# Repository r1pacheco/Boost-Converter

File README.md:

# Boost-Converter

<h3>This board was designed specifically for the R3 rover and has major restraints that were followed: </h3>

* Maximum dimensions of 42mm x 48mm x 23mm to remain inside the restrictions of the PDB (Power Distribution Board)
* Header space is required so parts do not overlap or bump edges as it is a tight fit within the chasis and the Molex connectors 
* Needs to handle a minimum of 5 amps and increase voltage from 15 to 24 volts minimum (my actual design uses a 5KΩ potentiometer to vary the desired voltage at the output, to make it more flexible for future use if needed)

|Top Side|Bottom Side|
|---|---|
|||  

*Click the above photos for a larger view*

<h3>Details and considerations made to improve the boards design and functionality:</h3>

* Thick traces or polygons are used to handle large current as well as act as heat displacers 
* Room for large external heat sinks was needed to help cool down the MOSFET and large diode on the board since they handle the bulk of the current
* Vias were also used to help give direct air flow to the main IC and fuse holder 
* a physical cutout (notch) was placed in the PCB beside the horizontal fuse holder, making it easier to set/remove the fuses (they can be tight sometimes)
* Large polygons were used where the most current would travel to make sure traces did not burn up and can disipate as much heat as possible
* all large capacitors/inductors were kept to one side of the board so they would not interfere with external Molex connectors on the PDB board. This is needed since the right side of the board will be overlapping pre-existing components and we needed the compensated space
* LED indication tells the user if the board is being used and is working properly
* overall board size was given tolerances of 1mm x 1mm x 1mm so they did not interfere with other external boards. Chamfers were also added for the same reason

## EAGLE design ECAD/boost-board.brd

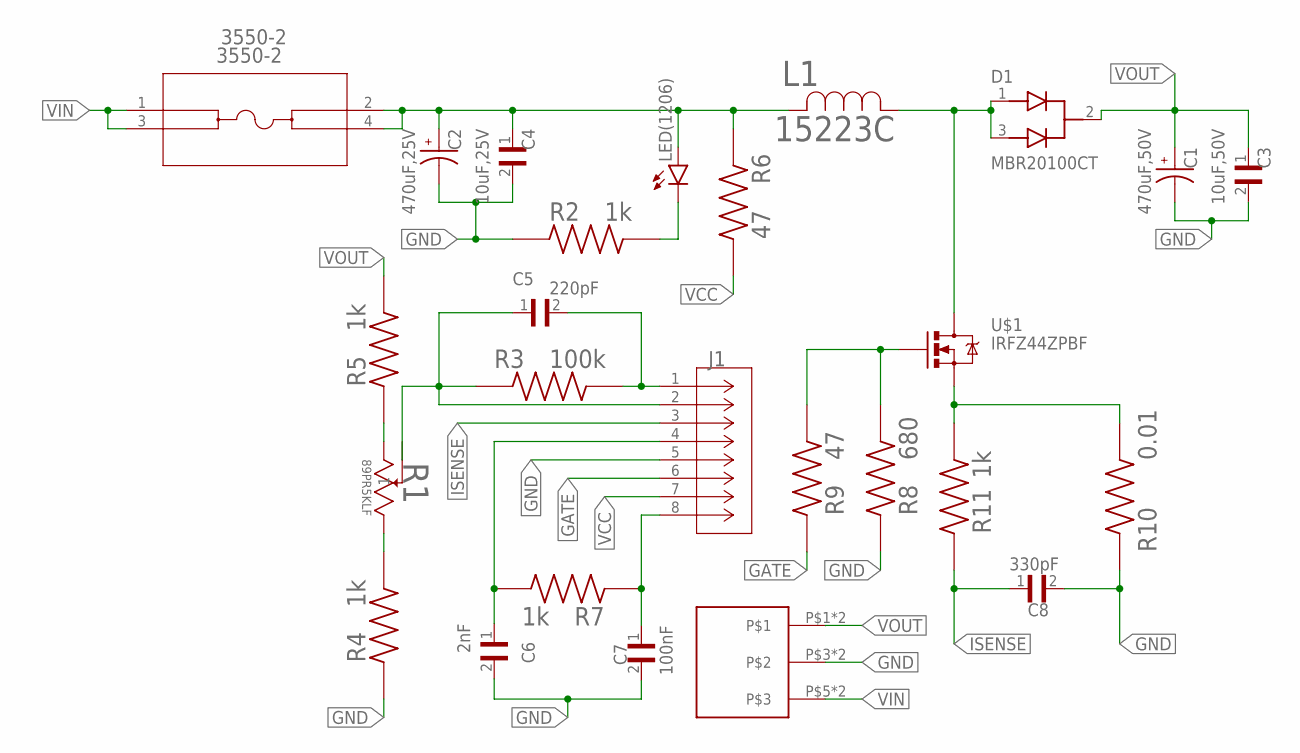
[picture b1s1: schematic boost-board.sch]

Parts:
3550-2: 3550-2; 3550-2_KEY
C1: 470uF,50V; CAPPRD500W60D1250H2200
C2: 470uF,25V; CAPPRD500W60D1000H1800
C3: 10uF,50V; CAPC3216X88N
C4: 10uF,25V; CAPC3216X88N
C5: 220pF; CAPC3216X88N
C6: 2nF; CAPC3216X88N
C7: 100nF; CAPC3216X88N
C8: 330pF; CAPC3216X88N
D1: MBR20100CT; TO254P1066X482X2286-3
J1: DILB8P-223TLF; CONN_DILB8P-223TLF_AMP
L1: 15223C; 15223C_MUR
LED(1206): LED-FKIT-1206; FKIT-LED-1206
R1: 89PR5KLF; RES3_89P_TTE
R2, R4, R5, R7, R11: 1k; RESC3216X70N
R3: 100k; RESC3216X70N
R6, R9: 47; RESC3216X70N
R8: 680; RESC3216X70N
R10: 0.01; RESC3216X70N
U$1: IRFZ44ZPBF; TO-220
U$2: FX30B-3S-3.81DSA; FX30B-4S-3.81DSA

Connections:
GATE: J1.6, R9.1
GND: C1.N, C2.N, C3.2, C4.2, C6.2, C7.2, C8.2, J1.5, R2.1, R4.1, R8.1, R10.1, U$2.P$3, U$2.P$4
ISENSE: C8.1, J1.3, R11.1
unnamed: C5.1, J1.2, R1.2, R3.1
unnamed: C5.2, J1.1, R3.2
unnamed: R1.1 (3), R4.2
unnamed: R1.3 (1), R5.1
unnamed: R8.2, R9.2, U$1.1 (G)
unnamed: D1.1 (ANODE1), D1.3 (ANODE2), L1.1, U$1.2 (D)
unnamed: C7.1, J1.8, R7.1
unnamed: LED(1206).C, R2.2
unnamed: R10.2, R11.2, U$1.3 (S)
unnamed: 3550-2.2, 3550-2.4, C2.P, C4.1, L1.2, LED(1206).A, R6.2
unnamed: C6.1, J1.4, R7.2
VCC: J1.7, R6.1
VIN: 3550-2.1, 3550-2.3, U$2.P$5, U$2.P$6
VOUT: C1.P, C3.1, D1.2 (COMMON_CATHODE), R5.2, U$2.P$1, U$2.P$2

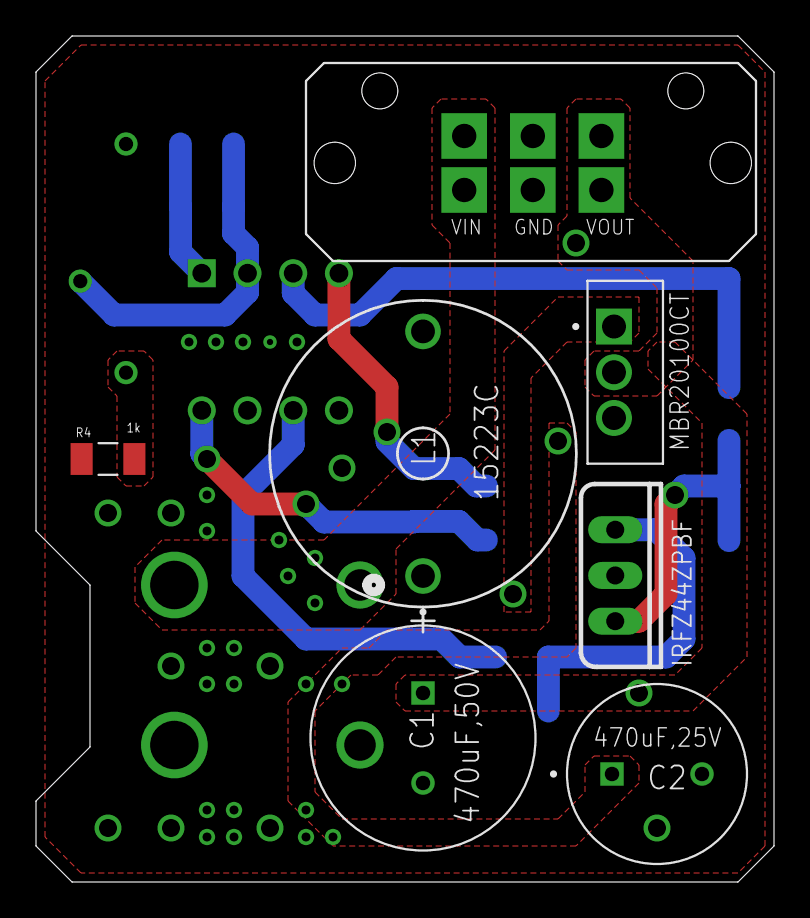
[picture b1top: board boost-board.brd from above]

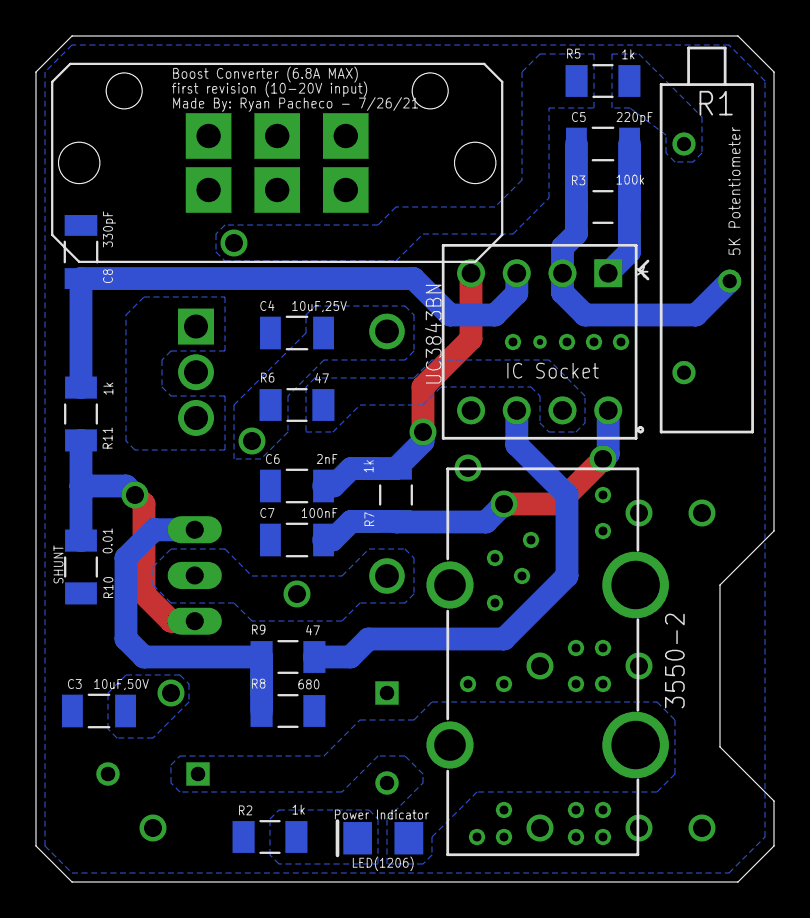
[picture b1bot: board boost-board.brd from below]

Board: 2 copper layers, 41.0 x 47.0 mm, 26 parts (20 on the bottom side), 17 nets.

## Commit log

2021-10-03 first push

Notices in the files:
parts and their libraries:
SparkFun-LED: Licensing: Creative Commons ShareAlike 4.0 International - https://creativecommons.org/licenses/by-sa/4.0
COPYRIGHT: Copyright (C) 2018 Accelerated Designs. All rights reserved
COPYRIGHT: Copyright (C) 2016 Accelerated Designs. All rights reserved
